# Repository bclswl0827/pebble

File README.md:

# Pebble

An another BLE tracking tag.

Pebble broadcasts in the OpenHaystack format and uses Apple's Find My network for location reports. This project also provides a modified version of OpenTagViewer for Android devices, which fixed the -80045 rejection error returned by Apple GSA.

## IC Design

| Component                         | Purpose                                                                                                                             |
| --------------------------------- | ----------------------------------------------------------------------------------------------------------------------------------- |
| Renesas **DA14531-00000FX2**      | BLE 5.1 SoC for Find My advertising, power management, and battery voltage measurement                                              |
| ST **LIS2DW12TR**                 | Low-power three-axis accelerometer connected over I²C for shake detection and interrupt wakeup                                      |
| (Optional) Winbond **W25X20CLSN** | 2 Mbit SPI Flash for boot firmware; marked DNP (do not populate) in the current BOM. The DA14531's internal OTP can be used instead |

The [hardware/](hardware/) directory contains the [schematic PDF](hardware/Pebble.pdf), KiCad design files, [BOM](hardware/Pebble.csv), and [Gerber files](hardware/gerber/).

## Usage

### 1. Set Up the Development Environment and SDK

Install [PlatformIO Core](https://docs.platformio.org/en/latest/core/installation/index.html) 6.1 or later and [Go](https://go.dev/dl/) 1.25 or later. A CMSIS-DAP SWD programmer is required for uploading firmware.

The Renesas SDK is not included in this repository. Download and extract it separately:

1. Open the [Renesas DA14531 product page](https://www.renesas.com/en/products/da14531) and find **DA145xx SDK 6.0.24.1464** under software and tools. Sign in if prompted and download `SDK_6.0.24.1464.zip`.
2. Place the ZIP in `firmware/platforms/da14531/vendor/` and extract it there. Run this command from the repository root:

   ```sh
   unzip firmware/platforms/da14531/vendor/SDK_6.0.24.1464.zip -d firmware/platforms/da14531/vendor/
   ```

3. Preserve the archive's directory structure. The extracted files should look like this:

   ```text
   firmware/platforms/da14531/vendor/
   ├── SDK_6.0.24.1464.zip
   └── DA145xx_SDK/
       └── 6.0.24.1464/
           ├── sdk/
           │   └── platform/include/da14531.h
           └── config/
               └── toolbox_resources/DA1453x/common/jtag_programmer_531.bin
   ```

The default SDK path is configured in [firmware/platformio.ini](firmware/platformio.ini):

```ini
custom_sdk_dir = platforms/da14531/vendor/DA145xx_SDK/6.0.24.1464
```

If you store the SDK elsewhere, update `custom_sdk_dir` to point to the version directory containing both `sdk/` and `config/`. Relative paths are resolved from `firmware/`.

### 2. Generate Your Find My Keys

Run from the repository root:

```sh
cd firmware/tools/findmy-keygen
go run . -p pebble
cp output/pebble/pebble_findmy_key.h ../../include/findmy_key.h
cd ../../..
```

- `pebble_findmy_key.h`: Public advertising key; copy it into the firmware before rebuilding.
- `pebble.keys`: Key file to import on Android.
- `pebble_devices.json`: Device file for Macless Haystack and compatible tools.

Files are saved to `firmware/tools/findmy-keygen/output/pebble/`. Use a separate key for each tag. The tool refuses to overwrite an existing output directory, so choose another `-p` name for subsequent tags. Keep the `.keys` and JSON files private: they contain private keys. The firmware currently broadcasts a single fixed key without rotation.

### 3. Build and Upload

Power the board and connect the CMSIS-DAP programmer's GND, SWCLK, and SWDIO to **TP1, TP2, and TP3**, respectively. SWD remains available for approximately **10 seconds after startup** before low-power sleep disables it. If the programmer cannot connect, power-cycle the board and retry.

Select an environment for your hardware. Each command builds and uploads the firmware:

| Environment | Command (from the repository root)               | Use case                                                                            |
| ----------- | ------------------------------------------------ | ----------------------------------------------------------------------------------- |
| SRAM        | `pio run -d firmware -e da14531_sram -t upload`  | Temporary development runs; lost on power-off; no external Flash required           |
| SPI Flash   | `pio run -d firmware -e da14531_flash -t upload` | Persistent, rewritable firmware; requires a populated W25X20CL; default environment |
| OTP         | `pio run -d firmware -e da14531_otp -t upload`   | Internal one-time-programmable memory for finalized firmware                        |

The OTP environment defaults to `custom_otp_confirm = no`, which checks the OTP without writing it. To program it permanently, change this value to `i_understand_otp_is_permanent` before uploading. The programmed firmware and key cannot be replaced afterward.

### 4. Operation and LED Indicators

- **Startup:** All three LEDs blink 10 times after the accelerometer initializes successfully.
- **Battery check:** Shake continuously for about 5 seconds. The LEDs show the battery level for about 5 seconds: all three at 2.9 V or above, yellow and red from 2.8 V to below 2.9 V, and red only below 2.8 V.
- **Nearby finding:** Tap **Ring** in OpenTagViewer to blink all three LEDs for about 10 seconds. Pebble responds with flashing LEDs; the board has no buzzer.

## Android Viewer

Use [OpenTagViewer](https://github.com/parawanderer/OpenTagViewer). This repository includes an [arm64-v8a debug APK](firmware/tools/OpenTagViewer-6100a00-arm64-v8a-debug.apk) for Android devices with ARM64 support.

1. Install the APK, sign in with an Apple account that has two-factor authentication enabled, and complete verification.
2. Transfer the generated `pebble.keys` file to your phone.
3. In the map or device list menu, select **Add OpenHaystack key (.keys)**, choose the file, and name the tag. Pebble uses user-generated keys, so it must be imported manually rather than discovered through iCloud.
4. Grant the requested Bluetooth permissions. When near the tag, view its signal strength and battery status or tap **Ring** to trigger the LEDs.

In the screenshot, **Nearby** means the phone detected the tag over Bluetooth. The dots indicate signal strength, and **Battery full** is the battery status carried in the advertisement. Use **Location History** to view past locations, **Refresh** to fetch location updates, and **Ring** to blink the tag's LEDs.

Remote location reports come from nearby Apple devices through the Find My network; update timing depends on surrounding devices and network conditions. Bluetooth detection and nearby finding require the phone to be within range of the tag.

## Changes

### Firmware

- Based on the Renesas SDK's `ble_app_noncon` example, with Pebble board configuration, PlatformIO integration, and CMSIS-DAP uploads to SRAM, SPI Flash, and OTP.
- Adds OpenHaystack advertising and a key generation tool, while keeping advertising connectable so DULT control commands can trigger LED finding.
- Adds LIS2DW12 interrupt wakeup, sustained shake detection, and low-power sleep. Battery indicators and advertisements reflect measured voltage; connection timeouts and advertising recovery help keep the tag discoverable.

### OpenTagViewer

This modified OpenTagViewer build draws on [sacca97/os-findmy-e](https://github.com/sacca97/os-findmy-e) for Mac/CoreADI emulation, Apple sign-in fixes, and CloudKit compatibility. Its native CoreADI implementation is a C++ port of that project's Rust `adi-core`.

The bundled APK is based on `6100a00` ([PR #274](https://github.com/parawanderer/OpenTagViewer/pull/274)). A [patch from `f5b09f7` to that revision](firmware/tools/OpenTagViewer-f5b09f7-to-pr274-6100a00.patch) is included. Its main changes are:

- Runs CoreADI through a Unicorn-based Mac emulator to generate Anisette data locally for new sign-ins, while preserving the original authentication provider for existing sessions.
- Fixes two-factor authentication handling when Apple returns `hsc = 409` during sign-in.
- Fixes compatibility between the emulated Mac's device identifier and CloudKit's UUID requirements.

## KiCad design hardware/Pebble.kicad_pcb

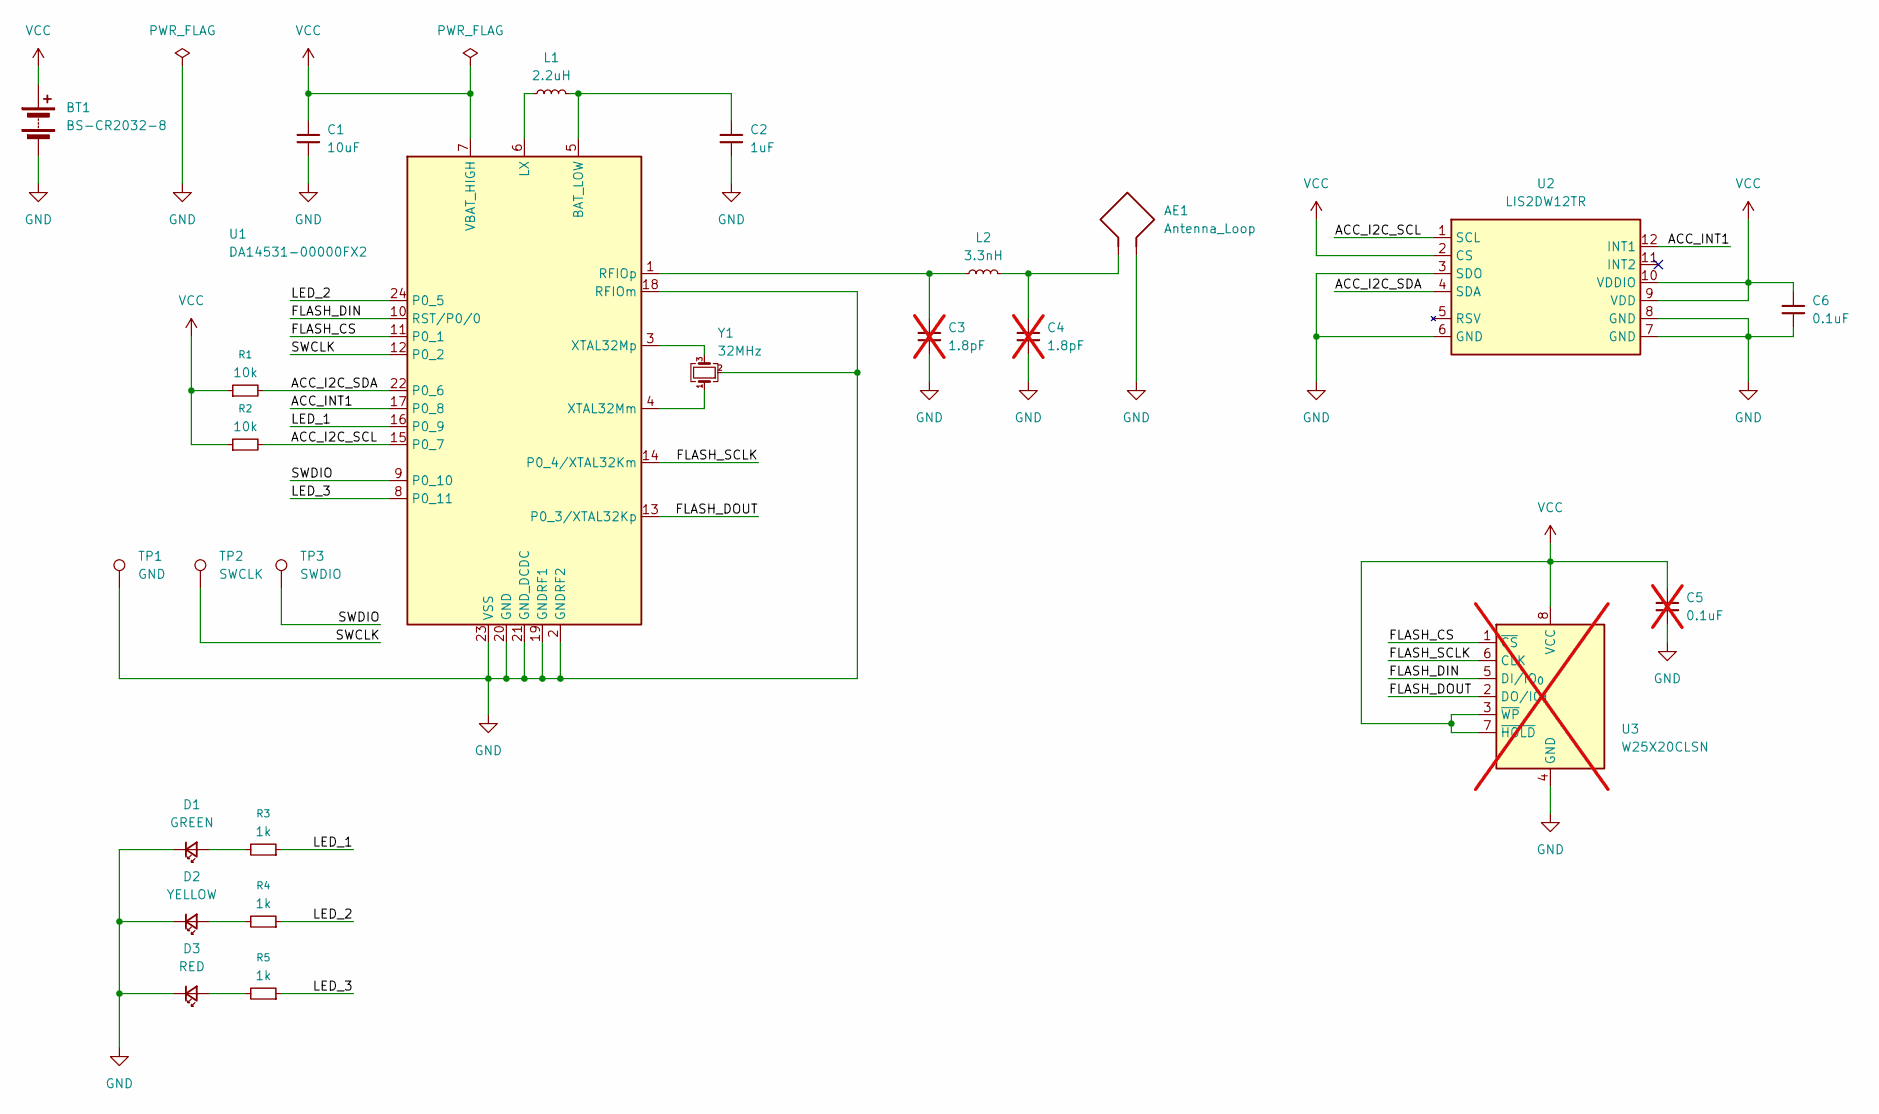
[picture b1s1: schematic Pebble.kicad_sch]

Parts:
AE1: Antenna_Loop; Texas_SWRA117D_2.4GHz_Left
BT1: BS-CR2032-8; BAT-SMD_BS-CR2032-8
C1: 10uF; C_0603_1608Metric
C2: 1uF; C_0603_1608Metric
C3, C4: 1.8pF; C_0603_1608Metric; not fitted
C5: 0.1uF; C_0603_1608Metric; not fitted
C6: 0.1uF; C_0603_1608Metric
D1: GREEN; LED_0603_1608Metric
D2: YELLOW; LED_0603_1608Metric
D3: RED; LED_0603_1608Metric
L1: 2.2uH; L_0603_1608Metric
L2: 3.3nH; L_0603_1608Metric
R1, R2: 10k; R_0603_1608Metric
R3, R4, R5: 1k; R_0603_1608Metric
TP1: GND; TestPoint_Pad_D1.0mm
TP2: SWCLK; TestPoint_Pad_D1.0mm
TP3: SWDIO; TestPoint_Pad_D1.0mm
U1: DA14531-00000FX2; FCGQFN-24_L3.0-W2.2-P0.40-BL
U2: LIS2DW12TR; LGA-12_2x2mm_P0.5mm
U3: W25X20CLSN; SOIC-8_3.9x4.9mm_P1.27mm; not fitted
Y1: 32MHz; Crystal_SMD_SeikoEpson_TSX3225-4Pin_3.2x2.5mm

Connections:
/ACC_I2C_SCL: R2.2, U1.15 (P0_7), U2.1 (SCL)
/ACC_I2C_SDA: R1.2, U1.22 (P0_6), U2.4 (SDA)
/ACC_INT1: U1.17 (P0_8), U2.12 (INT1)
/FLASH_CS: U1.11 (P0_1), U3.1 (~CS)
/FLASH_DIN: U1.10 (RST/P0/0), U3.5 (DI/IO_{0})
/FLASH_DOUT: U1.13 (P0_3/XTAL32Kp), U3.2 (DO/IO_{1})
/FLASH_SCLK: U1.14 (P0_4/XTAL32Km), U3.6 (CLK)
/LED_1: R3.1, U1.16 (P0_9)
/LED_2: R4.1, U1.24 (P0_5)
/LED_3: R5.1, U1.8 (P0_11)
/SWCLK: TP2.1 (1_1), U1.12 (P0_2)
/SWDIO: TP3.1 (1_1), U1.9 (P0_10)
GND: AE1.2, BT1.2 (-), C1.2, C2.2, C3.2, C4.2, C5.2, C6.2, D1.1 (K), D2.1 (K), D3.1 (K), TP1.1 (1_1), U1.2 (GNDRF2), U1.18 (RFIOm), U1.19 (GNDRF1), U1.20 (GND), U1.21 (GND_DCDC), U1.23 (VSS), U2.3 (SDO), U2.6 (GND), U2.7 (GND), U2.8 (GND), U3.4 (GND), Y1.2 (G), Y1.4 (G)
unnamed: AE1.1, C4.1, L2.2
unnamed: D1.2 (A), R3.2
unnamed: D2.2 (A), R4.2
unnamed: D3.2 (A), R5.2
unnamed: C2.1, L1.2, U1.5 (BAT_LOW)
unnamed: L1.1, U1.6 (LX)
unnamed: C3.1, L2.1, U1.1 (RFIOp)
unnamed: U1.4 (XTAL32Mm), Y1.1
unnamed: U1.3 (XTAL32Mp), Y1.3
VCC: BT1.1 (+), C1.1, C5.1, C6.1, R1.1, R2.1, U1.7 (VBAT_HIGH), U2.2 (CS), U2.9 (VDD), U2.10 (VDDIO), U3.3 (~WP), U3.7 (~HOLD), U3.8 (VCC)

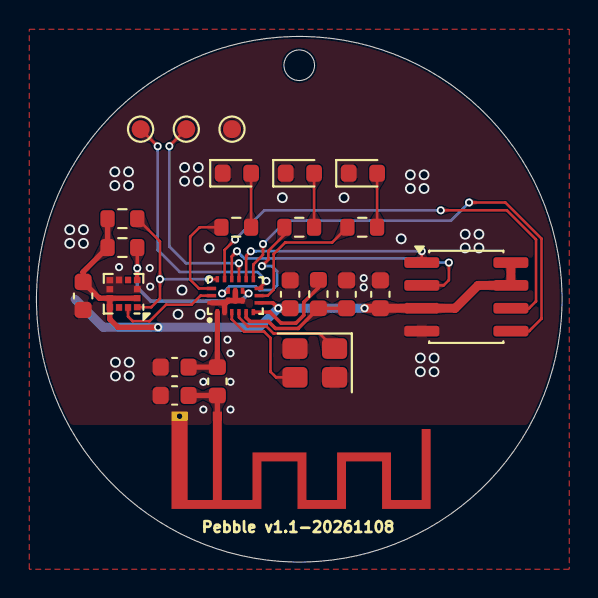
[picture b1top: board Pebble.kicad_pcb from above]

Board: 2 copper layers, 29.2 x 29.2 mm, 25 parts (1 on the bottom side), 23 nets.

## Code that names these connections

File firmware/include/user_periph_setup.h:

#ifndef USER_PERIPH_SETUP_H
#define USER_PERIPH_SETUP_H

#include <stdint.h>
#include "gpio.h"

#define LED_PORT GPIO_PORT_0
#define LED_1_PIN GPIO_PIN_9
#define LED_2_PIN GPIO_PIN_5
#define LED_3_PIN GPIO_PIN_11

#define LED_1 (1U << 0)
#define LED_2 (1U << 1)
#define LED_3 (1U << 2)
#define LED_ALL (LED_1 | LED_2 | LED_3)

/* LIS2DW12: I2C address 0x18 (SA0 = GND), INT2 not connected. */
#define ACC_PORT GPIO_PORT_0
#define ACC_SCL_PIN GPIO_PIN_7
#define ACC_SDA_PIN GPIO_PIN_6
#define ACC_INT1_PIN GPIO_PIN_8

/* W25X20CL boot Flash. */
#define SPI_EN_PORT GPIO_PORT_0
#define SPI_EN_PIN GPIO_PIN_1
#define SPI_CLK_PORT GPIO_PORT_0
#define SPI_CLK_PIN GPIO_PIN_4
#define SPI_DO_PORT GPIO_PORT_0
#define SPI_DO_PIN GPIO_PIN_0
#define SPI_DI_PORT GPIO_PORT_0
#define SPI_DI_PIN GPIO_PIN_3

void leds_set(uint8_t mask);
uint8_t leds_get(void);
void periph_init(void);
void GPIO_reservations(void);

#endif
